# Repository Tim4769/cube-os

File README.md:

# Cube OS

## Members

- Tim
- Pat
- Taiyo

## Description

Cube OS is a desktop robot of 80 x 80 x 80 mm controlled by two legs. It can walk and communicate with other Cube OS robots through online servers using a custom PCB with an ESP32 microcontroller. It supports voice messages, text messages, and remote control features, helping friends stay connected even when they are far apart.

## Features

- Wi-Fi communication between robots via an online server.
- Two 9 g servos power a four-bar walking linkage for bipedal locomotion.
- IMU-assisted stepping, turning, fall detection, and recovery for inertial gait control.
- Ambient Rest Mode with light-aware quiet, privacy, and do-not-disturb behavior.
- Desk climate sensing for local humidity and temperature data.
- Voice Mailbox using the integrated microphone and speaker to record and replay voice notes from friends.
- USB-C power workflow for battery-powered operation, serial debugging, charging, and flashing.
- Camera sharing with OV2640 pictures or brief videos sent to friends or the dashboard.
- Four-face display OS with widgets, expressions, friend feeds, time, status, and air data.
- Remote control so friends can control another Cube OS and interact from far away.

## Justification

Some of our team members are graduating from high school and heading to college after 7 years together at the same school, and we thought, why do not we build something to keep our connection more real and maintain our friend group? Social media and group chats alone make it hard to keep the connection physical, and we will not always have time to fly to each other's cities to meet.

With Cube OS, we aim to keep annoying each other like we used to, in a friendly manner, by controlling each other's robots and sending random noises and messages at 2 am, like crashing into each other's dorm rooms as we used to. With its extra features, it can also serve as a handy desktop companion for productivity or just an accessory for your desk.

## BOM Breakdown

| Item | Qty | Estimate |
| --- | ---: | ---: |
| PCB, minimum production amount | 2 | 144 USD |
| 9 g micro servo motors | 2 | 8 USD |
| OV2640 camera | 1 | 5 USD |
| AS02504AR speaker | 1 | 5 USD |
| 1S 3.7 V LiPo battery | 1 | 6 USD |
| ER-TFT1.54-2 display panels | 4 | 24 USD |
| **Total** |  | **192 USD** |

## Current Status Photos

Current mechanical linkage prototype.

Current PCB layout and component placement.

Current assembled Rev A PCB during USB, firmware, and Wi-Fi power bring-up.

## Project Files

Short index of the main current files. Directory paths, placeholder files, metadata files, scaffold code, TODO files, and planning notes are intentionally excluded.

- PCB source: `PCB/Rev A/source/Cube OS/Cube OS.kicad_pro`, `PCB/Rev A/source/Cube OS/Cube OS.kicad_sch`, `PCB/Rev A/source/Cube OS/Cube OS.kicad_pcb`
- PCB fabrication package: `PCB/Rev A/gerbers/Gerber.zip`, `PCB/Rev A/production/BOM.csv`, `PCB/Rev A/production/CPL.csv`, `PCB/Rev A/production/fabrication_notes.md`
- PCB order package: `PCB/Rev A/order/BOM_manufacture.xls`, `PCB/Rev A/order/ordering contract.pdf`
- PCB 3D export and linked models: `PCB/Rev A/3d_models/PCB 3d model.step`, `PCB/Rev A/source/Cube OS/3D models/`
- Firmware bring-up: `Firmware/platformio.ini`, `Firmware/src/main.cpp`, `Firmware/src/config.h`, `Firmware/src/`
- Sourcing and budget: `BOM/bom.csv`, `BOM/sourcing_notes.md`
- Mechanical assembly: `CAD/Legs/Linkage V2/Assembly/Stepping foot linkage prototype v2.step`
- Current status photos: `Media/Mechanical status 20260511222505_905_44.jpg`, `Media/PCB status 2026-05-28 at 6.02.45 PM.png`, `Media/PCB status 2026-07-15 at 9.23.13 PM.jpg`

## Git LFS

Large binary project assets are tracked with Git LFS through `.gitattributes`, including status photos, CAD/STEP exports, Gerber/drill manufacturing files, archives, PDFs, and spreadsheet order records.

## Placeholder, Scaffold, And Planning Content

These paths are not listed as active project files because they currently contain placeholder files, metadata files, TODO-only files, scaffold code, or planning notes. There is no final project content inside them yet.

- `Software/`
- `Software/src/`
- `Software/screenshots/`

Also excluded from the active project list: `CAD/Legs/Linkage V2/Components/Placeholder Bar.step`.

## License

MIT. See `LICENSE`.

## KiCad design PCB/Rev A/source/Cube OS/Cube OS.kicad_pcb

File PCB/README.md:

# PCB

Cube OS Rev A electrical design, KiCad source, Gerbers, PCBA files, footprints, and linked STEP models.

## Rev A

- Project: `Cube OS`
- KiCad: 9.0
- Board: 60.05 mm x 60.05 mm, 4-layer FR4, 1.599 mm
- Finish: HAL lead-free
- Assembly: top-side SMT and connectors
- Fabrication archive: `Rev A/gerbers/Gerber.zip`
- Order package: `Rev A/order/`

## Active Files

- Source: `Rev A/source/Cube OS/`
- BOM: `Rev A/production/BOM.csv`
- CPL: `Rev A/production/CPL.csv`
- Notes: `Rev A/production/fabrication_notes.md`
- Gerbers: `Rev A/gerbers/Gerber/`
- 3D board export: `Rev A/3d_models/PCB 3d model.step`
- Order records: `Rev A/order/`
- Template/reference data: `Template/`

## Electronics

| Area | Parts |
| --- | --- |
| MCU | ESP32-S3-WROOM-1-N8R8 |
| Displays | Four display FPCs |
| Camera | OV2640 via Amphenol F32R connector |
| Sensors | SHT45, VEML7700, ISM330DHCX, ICS-43434, 10 kOhm NTC |
| Audio | MAX98357A I2S amplifier, JST speaker connector |
| Motion | Two 3-pin servo headers |
| Power | USB-C, 1S LiPo, BQ24074, TPS63802, LDLN025M25R, TPS7A0212 |
| Controls | JS202011JAQN, SPPJ320600 |

## Production Snapshot

- BOM line items: 38
- CPL top-side placements: 45, excluding H1-H4 mounting holes
- Local footprints: `Rev A/source/Cube OS/Cube_OS_Footprint.pretty/`
- Local STEP models: `Rev A/source/Cube OS/3D models/`

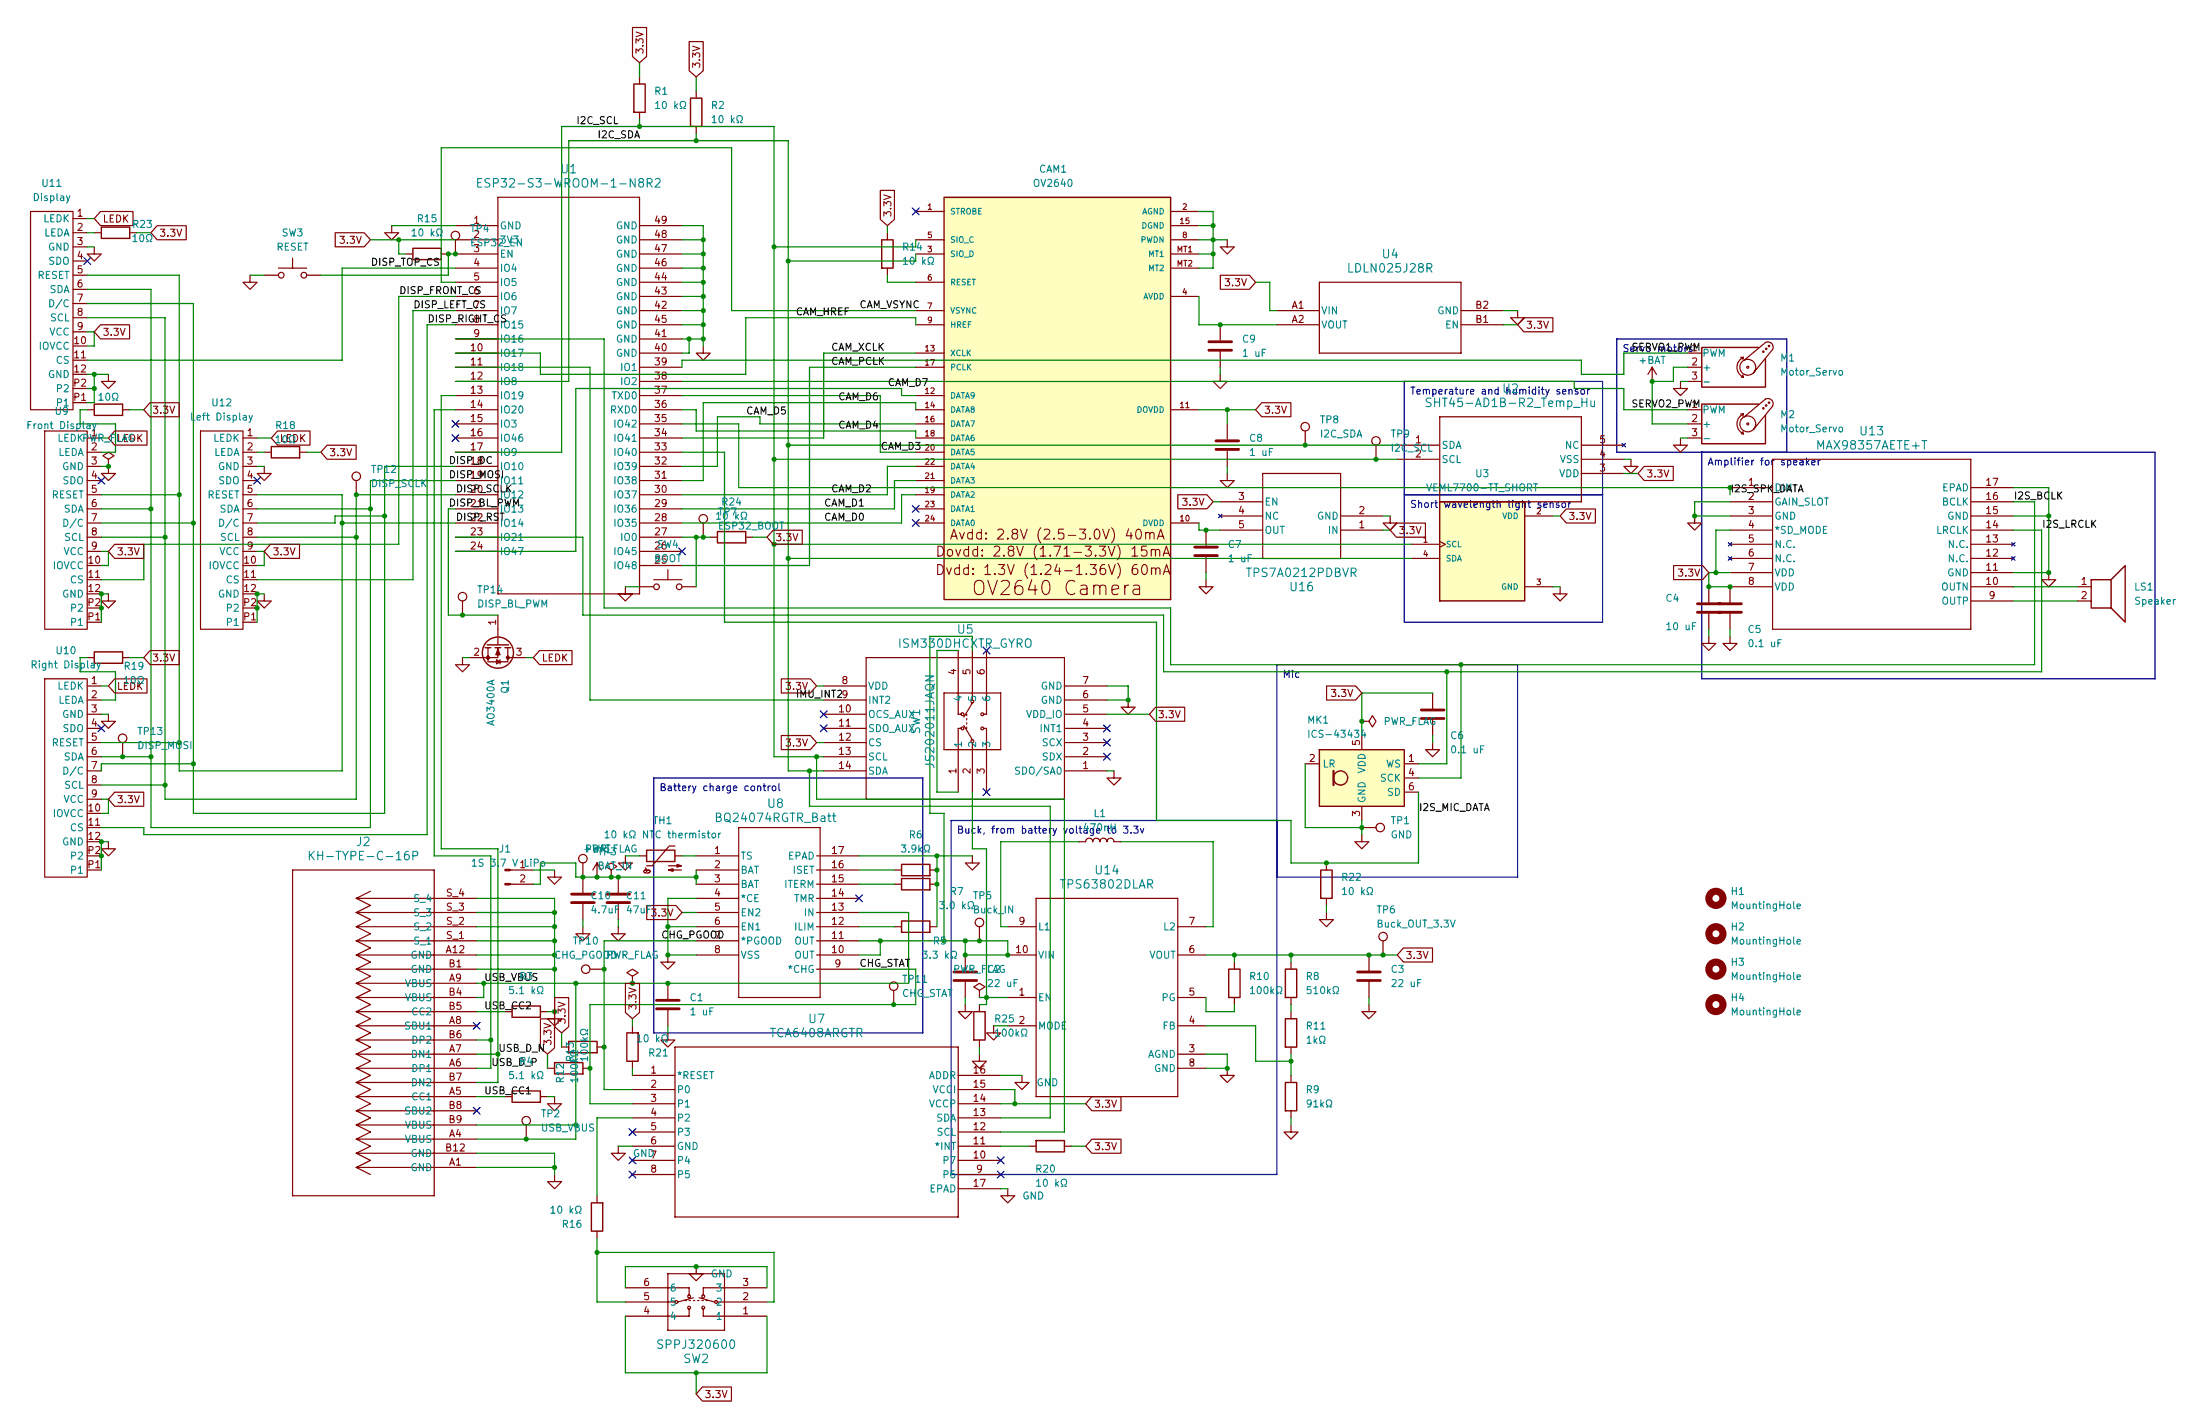
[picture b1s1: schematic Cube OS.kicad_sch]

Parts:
C1, C7, C8, C9: 1 uF; C_0402_1005Metric; JLCPCB C52923
C2, C3: 22 uF; C_0603_1608Metric; JLCPCB C59461
C4: 10 uF; C_0402_1005Metric; JLCPCB C15525
C5, C6: 0.1 uF; C_0402_1005Metric; JLCPCB C1525
C10: 4.7uF; C_0402_1005Metric; JLCPCB C23733
C11: 47uF; C_0805_2012Metric; JLCPCB C16780
CAM1: OV2640; AMPHENOL_F32R-1A7H1-11024; JLCPCB C3167938
H1, H2, H3, H4: MountingHole; MountingHole_2.2mm_M2
J1: 1S 3.7 V LiPo; JST_PH_B2B-PH-K_1x02_P2.00mm_Vertical; JLCPCB C131337
J2: KH-TYPE-C-16P; CONN_KH-TYPE-C_SKE; JLCPCB C709357
L1: 470nH; IND_MWSA0603S_SNL; JLCPCB C408439
LS1: Speaker; JST_PH_B2B-PH-K_1x02_P2.00mm_Vertical; JLCPCB C131337
M1, M2: Motor_Servo; PinHeader_1x03_P2.54mm_Vertical; JLCPCB C49257
MK1: ICS-43434; InvenSense_ICS-43434-6_3.5x2.65mm; JLCPCB C5656610
Q1: AO3400A; SOT-23; JLCPCB C20917
R1, R2, R14, R15, R16, R20, R21, R22, R24: 10 kΩ; R_0402_1005Metric; JLCPCB C25744
R3, R4: 5.1 kΩ; R_0402_1005Metric; JLCPCB C25905
R5: 3.3 kΩ; R_0402_1005Metric; JLCPCB C25890
R6: 3.9kΩ; R_0603_1608Metric; JLCPCB C23018
R7: 3.0 kΩ; R_0603_1608Metric; JLCPCB C4211
R8: 510kΩ; R_0603_1608Metric; JLCPCB C23192
R9: 91kΩ; R_0603_1608Metric; JLCPCB C23265
R10, R12, R13, R25: 100kΩ; R_0402_1005Metric; JLCPCB C25741
R11: 1kΩ; R_0402_1005Metric; JLCPCB C11702
R17, R18, R19, R23: 10Ω; R_0603_1608Metric; JLCPCB C22859
SW1: JS202011JAQN; SWITCH_011CQN; JLCPCB C221662
SW2: SPPJ320600; SPPJ320600_AAL; JLCPCB C470431
SW3: RESET; SW_TS-1088_XNP; JLCPCB C720477
SW4: BOOT; SW_TS-1088_XNP; JLCPCB C720477
TH1: 10 kΩ NTC thermistor; R_0402_1005Metric; JLCPCB C77131
TP1: GND; TestPoint_Pad_1.0x1.0mm
TP2: USB_VBUS; TestPoint_Pad_1.0x1.0mm
TP3: BAT_IN; TestPoint_Pad_1.0x1.0mm
TP4: ESP32_EN; TestPoint_Pad_1.0x1.0mm
TP5: Buck_IN; TestPoint_Pad_1.0x1.0mm
TP6: Buck_OUT_3.3V; TestPoint_Pad_1.0x1.0mm
TP7: ESP32_BOOT; TestPoint_Pad_1.0x1.0mm
TP8: I2C_SDA; TestPoint_Pad_1.0x1.0mm
TP9: I2C_SCL; TestPoint_Pad_1.0x1.0mm
TP10: CHG_PGOOD; TestPoint_Pad_1.0x1.0mm
TP11: CHG_STAT; TestPoint_Pad_1.0x1.0mm
TP12: DISP_SCLK; TestPoint_Pad_1.0x1.0mm
TP13: DISP_MOSI; TestPoint_Pad_1.0x1.0mm
TP14: DISP_BL_PWM; TestPoint_Pad_1.0x1.0mm
U1: ESP32-S3-WROOM-1-N8R2; ESP32-S3-WROOM-1_EXP; JLCPCB C2913204
U2: SHT45-AD1B-R2_Temp_Hu; SHT4x_SEN; JLCPCB C5221601
U3: VEML7700-TT_SHORT; XDCR_VEML7700-TT; PARTREV 1.6; DigiKey_Part_Number 751-VEML7700-TTCT-ND
U4: LDLN025J28R; FLIPCHIP4_0P658X0P658_STM; JLCPCB C2971613
U5: ISM330DHCXTR_GYRO; LGA-14L_STM; JLCPCB C2655101
U7: TCA6408ARGTR; RGT16_1P45X1P45; JLCPCB C181499
U8: BQ24074RGTR_Batt; RGT16_1P7X1P7; JLCPCB C54313
U9: Front Display; CON_5034801200_MOL; JLCPCB C587969
U10: Right Display; CON_5034801200_MOL; JLCPCB C587969
U11: Display; CON_5034801200_MOL; JLCPCB C587969
U12: Left Display; CON_5034801200_MOL; JLCPCB C587969
U13: MAX98357AETE+T; 21-0136I_T1633-4_MXM; JLCPCB C910544
U14: TPS63802DLAR; DLA0010A; JLCPCB C2845237
U16: TPS7A0212PDBVR; SOT23_DBV_TEX; JLCPCB C5220172

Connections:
3.3V: C3.1, C4.1, C5.1, C6.1, C8.1, CAM1.11 (DOVDD), MK1.5 (VDD), R1.1, R2.1, R8.1, R10.1, R12.1, R13.1, R14.1, R15.1, R17.2, R18.2, R19.2, R20.1, R21.2, R23.2, R24.2, SW2.1, SW2.4, TP6.1, U1.2 (3V3), U2.3 (VDD), U3.2 (VDD), U4.A1 (VIN), U4.B1 (EN), U5.5 (VDD_IO), U5.8 (VDD), U5.12 (CS), U7.14 (VCCP), U7.15 (VCCI), U8.5 (EN2), U9.9 (VCC), U9.10 (IOVCC), U10.9 (VCC), U10.10 (IOVCC), U11.9 (VCC), U11.10 (IOVCC), U12.9 (VCC), U12.10 (IOVCC), U13.4 (*SD_MODE), U13.7 (VDD), U13.8 (VDD), U14.6 (VOUT), U16.1 (IN), U16.3 (EN)
+BAT: C10.1, C11.1, J1.2, M1.2 (+), M2.2 (+), TP3.1, U8.2 (BAT), U8.3 (BAT)
/CAM_D0: CAM1.19 (DATA2), U1.28 (IO35)
/CAM_D1: CAM1.21 (DATA3), U1.29 (IO36)
/CAM_D2: CAM1.22 (DATA4), U1.30 (IO37)
/CAM_D3: CAM1.20 (DATA5), U1.37 (TXD0)
/CAM_D4: CAM1.18 (DATA6), U1.36 (RXD0)
/CAM_D5: CAM1.16 (DATA7), U1.32 (IO39)
/CAM_D6: CAM1.14 (DATA8), U1.31 (IO38)
/CAM_D7: CAM1.12 (DATA9), U1.24 (IO47)
/CAM_HREF: CAM1.9 (HREF), U1.10 (IO17)
/CAM_PCLK: CAM1.17 (PCLK), U1.25 (IO48)
/CAM_VSYNC: CAM1.7 (VSYNC), U1.5 (IO5)
/CAM_XCLK: CAM1.13 (XCLK), U1.34 (IO41)
/CHG_PGOOD: R13.2, TP10.1, U7.2 (P0), U8.7 (*PGOOD)
/CHG_STAT: R12.2, TP11.1, U7.3 (P1), U8.9 (*CHG)
/DISP_BL_PWM: Q1.1 (G), TP14.1, U1.21 (IO13)
/DISP_DC: U1.18 (IO10), U9.7 (D/C), U10.7 (D/C), U11.7 (D/C), U12.7 (D/C)
/DISP_FRONT_CS: U1.6 (IO6), U9.11 (CS)
/DISP_LEFT_CS: U1.7 (IO7), U12.11 (CS)
/DISP_MOSI: TP13.1, U1.19 (IO11), U9.6 (SDA), U10.6 (SDA), U11.6 (SDA), U12.6 (SDA)
/DISP_RIGHT_CS: U1.8 (IO15), U10.11 (CS)
/DISP_RST: U1.22 (IO14), U9.5 (RESET), U10.5 (RESET), U11.5 (RESET), U12.5 (RESET)
/DISP_SCLK: TP12.1, U1.20 (IO12), U9.8 (SCL), U10.8 (SCL), U11.8 (SCL), U12.8 (SCL)
/DISP_TOP_CS: U1.4 (IO4), U11.11 (CS)
/I2C_SCL: CAM1.5 (SIO_C), R1.2, TP9.1, U1.17 (IO9), U2.2 (SCL), U3.1 (SCL), U5.13 (SCL), U7.12 (SCL)
/I2C_SDA: CAM1.3 (SIO_D), R2.2, TP8.1, U1.12 (IO8), U2.1 (SDA), U3.4 (SDA), U5.14 (SDA), U7.13 (SDA)
/I2S_BCLK: MK1.4 (SCK), U1.9 (IO16), U13.16 (BCLK)
/I2S_LRCLK: MK1.1 (WS), U1.23 (IO21), U13.14 (LRCLK)
/I2S_MIC_DATA: MK1.6 (SD), R22.1, U1.33 (IO40)
/I2S_SPK_DATA: U1.35 (IO42), U13.1 (DIN)
/IMU_INT2: U1.11 (IO18), U5.9 (INT2)
/SERVO1_PWM: M1.1 (PWM), U1.39 (IO1)
/SERVO2_PWM: M2.1 (PWM), U1.38 (IO2)
/USB_CC1: J2.A5 (CC1), R4.1
/USB_CC2: J2.B5 (CC2), R3.1
/USB_D_N: J2.A7 (DN1), J2.B7 (DN2), U1.13 (IO19)
/USB_D_P: J2.A6 (DP1), J2.B6 (DP2), U1.14 (IO20)
/USB_VBUS: C1.1, J2.A4 (VBUS), J2.A9 (VBUS), J2.B4 (VBUS), J2.B9 (VBUS), TP2.1, U8.13 (IN)
GND: C1.2, C2.2, C3.2, C4.2, C5.2, C6.2, C7.2, C8.2, C9.2, C10.2, C11.2, CAM1.2 (AGND), CAM1.8 (PWDN), CAM1.15 (DGND), CAM1.MT1, CAM1.MT2, J1.1, J2.A1 (GND), J2.A12 (GND), J2.B1 (GND), J2.B12 (GND), J2.S_1, J2.S_2, J2.S_3, J2.S_4, M1.3 (-), M2.3 (-), MK1.2 (LR), MK1.3 (GND), Q1.2 (S), R3.2, R4.2, R5.2, R6.2, R7.2, R9.2, R22.2, R25.2, SW2.3, SW2.6, SW3.1, SW4.1, TH1.1, TP1.1, U1.1 (GND), U1.40 (GND), U1.41 (GND), U1.42 (GND), U1.43 (GND), U1.44 (GND), U1.45 (GND), U1.46 (GND), U1.47 (GND), U1.48 (GND), U1.49 (GND), U2.4 (VSS), U3.3 (GND), U4.B2 (GND), U5.1 (SDO/SA0), U5.6 (GND), U5.7 (GND), U7.6 (GND), U7.16 (ADDR), U7.17 (EPAD), U8.4 (*CE), U8.6 (EN1), U8.8 (VSS), U8.17 (EPAD), U9.3 (GND), U9.12 (GND), U9.P1, U9.P2, U10.3 (GND), U10.12 (GND), U10.P1, U10.P2, U11.3 (GND), U11.12 (GND), U11.P1, U11.P2, U12.3 (GND), U12.12 (GND), U12.P1, U12.P2, U13.2 (GAIN_SLOT), U13.3 (GND), U13.11 (GND), U13.15 (GND), U13.17 (EPAD), U14.2 (MODE), U14.3 (AGND), U14.8 (GND), U16.2 (GND)
LEDK: Q1.3 (D), U9.1 (LEDK), U10.1 (LEDK), U11.1 (LEDK), U12.1 (LEDK)
unnamed: C9.1, CAM1.4 (AVDD), U4.A2 (VOUT)
unnamed: C7.1, CAM1.10 (DVDD), U16.5 (OUT)
unnamed: CAM1.6 (RESET), R14.2
unnamed: R8.2, R11.1
unnamed: R16.1, SW2.2, SW2.5
unnamed: SW1.1, SW1.4
unnamed: R15.2, SW3.2, TP4.1, U1.3 (EN)
unnamed: R24.1, SW4.2, TP7.1, U1.27 (IO0)
unnamed: R20.2, U7.11 (*INT)
unnamed: R21.1, U7.1 (*RESET)
unnamed: R16.2, U7.4 (P2)
unnamed: R5.1, U8.12 (ILIM)
unnamed: R6.1, U8.16 (ISET)
unnamed: R7.1, U8.15 (ITERM)
unnamed: TH1.2, U8.1 (TS)
unnamed: R17.1, U9.2 (LEDA)
unnamed: R19.1, U10.2 (LEDA)
unnamed: R23.1, U11.2 (LEDA)
unnamed: R18.1, U12.2 (LEDA)
unnamed: LS1.1, U13.10 (OUTN)
unnamed: LS1.2, U13.9 (OUTP)
unnamed: R25.1, SW1.2, U14.1 (EN)
unnamed: R9.1, R11.2, U14.4 (FB)
unnamed: L1.1, U14.9 (L1)
unnamed: L1.2, U14.7 (L2)
unnamed: R10.2, U14.5 (PG)
unnamed: C2.1, SW1.5, TP5.1, U8.10 (OUT), U8.11 (OUT), U14.10 (VIN)

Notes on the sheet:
Buck, from battery voltage to 3.3v
Battery charge control
Amplifier for speaker
Temperature and humidity sensor
Mic
Servo motors
Short wavelength light sensor

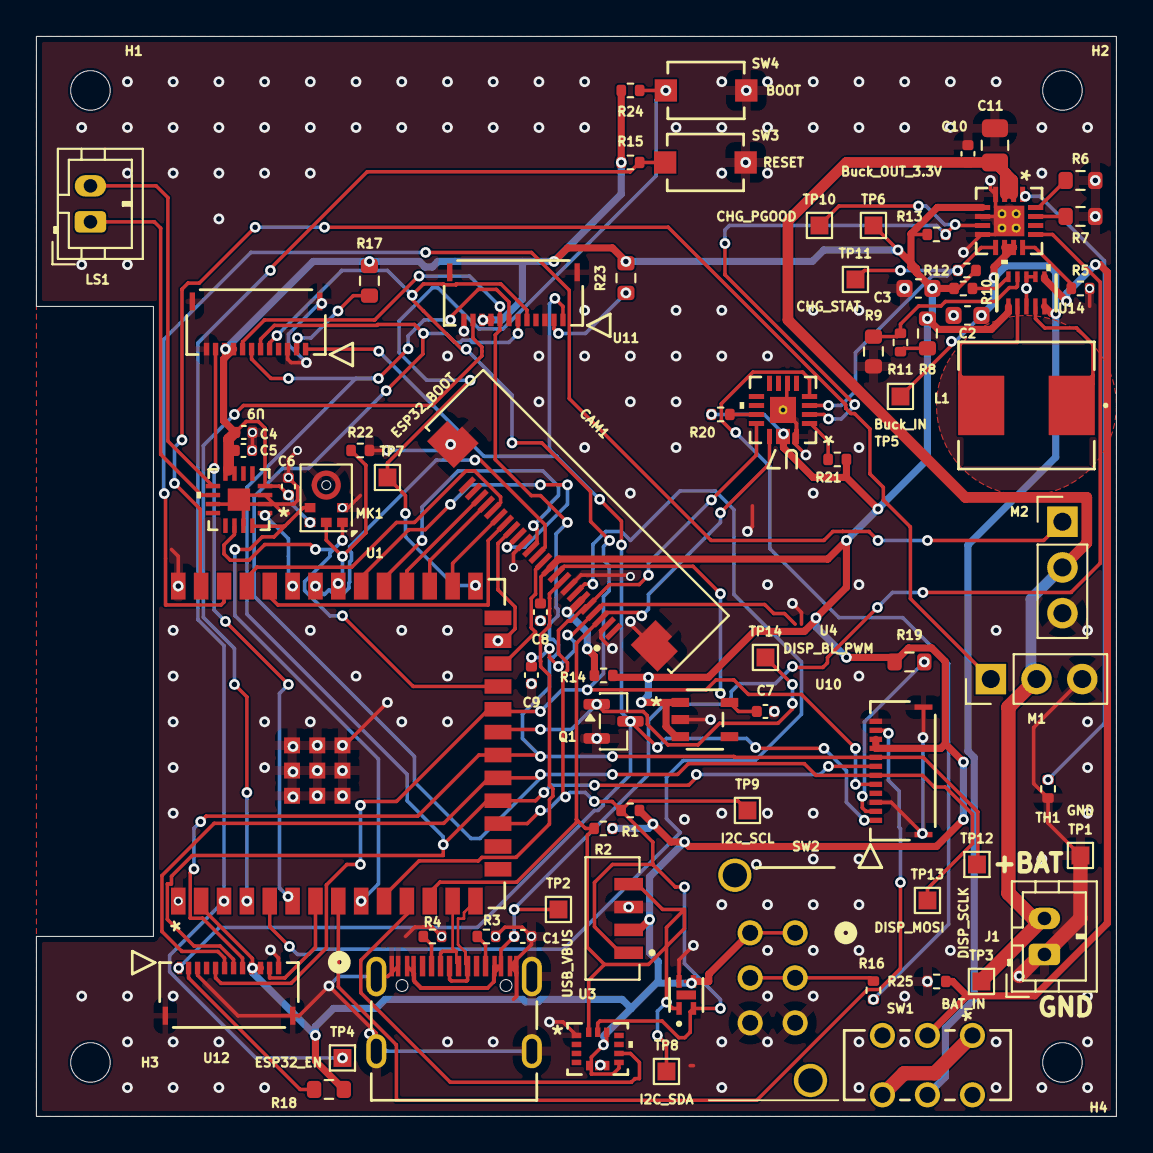
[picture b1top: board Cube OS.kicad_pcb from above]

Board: 4 copper layers, 60.0 x 60.0 mm, 82 parts (0 on the bottom side), 68 nets.

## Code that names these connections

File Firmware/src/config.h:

#pragma once

#define SERIAL_BAUD_RATE 115200

// Setup access point details. These are only used when the ESP32 needs Wi-Fi setup.
constexpr const char* AP_NAME = "CubeOS-Setup";
constexpr const char* AP_PASSWORD = "12345678";

// mDNS lets a browser open http://cubeos.local instead of typing the numeric IP address.
constexpr const char* MDNS_NAME = "cubeos";

// Names used inside ESP32 NVS flash storage for the saved Wi-Fi credentials.
constexpr const char* WIFI_NAMESPACE = "wifi";
constexpr const char* WIFI_SSID_KEY = "ssid";
constexpr const char* WIFI_PASSWORD_KEY = "password";
constexpr const char* WIFI_CONFIGURED_KEY = "configured";

// Timing values are in milliseconds.
constexpr unsigned long BOOT_STABILIZE_DELAY_MS = 3000;
constexpr unsigned long WIFI_CONNECT_TIMEOUT_MS = 15000;
constexpr unsigned long WIFI_CONNECT_CHECK_INTERVAL_MS = 500;
constexpr unsigned long MDNS_RETRY_INTERVAL_MS = 5000;

// The web server listens on port 80, the normal HTTP port.
constexpr int WEB_SERVER_PORT = 80;

constexpr int PIN_UNASSIGNED = -1;

// Rev A has no separate status LED GPIO in the schematic.
// Do not use GPIO48 for status LED: GPIO48 is CAM_PCLK.
constexpr int STATUS_LED_PIN = PIN_UNASSIGNED;

// Shared I2C/SCCB bus.
constexpr int I2C_SDA_PIN = 8;
constexpr int I2C_SCL_PIN = 9;

// Four display connectors share MOSI/SCLK/DC/reset/backlight and use separate CS pins.
constexpr int DISPLAY_TOP_CS_PIN = 4;
constexpr int DISPLAY_FRONT_CS_PIN = 6;
constexpr int DISPLAY_LEFT_CS_PIN = 7;
constexpr int DISPLAY_RIGHT_CS_PIN = 15;
constexpr int DISPLAY_DC_PIN = 10;
constexpr int DISPLAY_MOSI_PIN = 11;
constexpr int DISPLAY_SCLK_PIN = 12;
constexpr int DISPLAY_BACKLIGHT_PWM_PIN = 13;
constexpr int DISPLAY_RESET_PIN = 14;

// I2S audio: ICS-43434 microphone and MAX98357A speaker amplifier.
constexpr int I2S_BCLK_PIN = 16;
constexpr int I2S_LRCLK_PIN = 21;
constexpr int I2S_MIC_DATA_PIN = 40;
constexpr int I2S_SPK_DATA_PIN = 42;

// ISM330DHCX interrupt lines.
// INT1 is not connected in the latest Rev A schematic.
constexpr int IMU_INT1_PIN = PIN_UNASSIGNED;
constexpr int IMU_INT2_PIN = 18;

// Servo connector PWM pins.
constexpr int MOVEMENT_SERVO1_PWM_PIN = 1; // M1
constexpr int MOVEMENT_SERVO2_PWM_PIN = 2; // M2

// Only assign these after confirming which physical servo is left/right.
constexpr int MOVEMENT_LEFT_SERVO_PIN = PIN_UNASSIGNED;
constexpr int MOVEMENT_RIGHT_SERVO_PIN = PIN_UNASSIGNED;

// User/control and charger status lines are on the TCA6408 I2C GPIO expander,
// not direct ESP32 GPIOs.
constexpr int USER_SWITCH_PIN = PIN_UNASSIGNED;
constexpr int CHARGER_PGOOD_PIN = PIN_UNASSIGNED;
constexpr int CHARGER_STAT_PIN = PIN_UNASSIGNED;

constexpr int IO_EXPANDER_CHARGER_PGOOD_PIN = 0;
constexpr int IO_EXPANDER_CHARGER_STAT_PIN = 1;
constexpr int IO_EXPANDER_USER_SWITCH_PIN = 2;

// OV2640 camera parallel bus and clock/sync pins.
constexpr int CAMERA_D0_PIN = 35;
constexpr int CAMERA_D1_PIN = 36;
constexpr int CAMERA_D2_PIN = 37;
constexpr int CAMERA_D3_PIN = 43; // schematic pin function TXD0
constexpr int CAMERA_D4_PIN = 44; // schematic pin function RXD0
constexpr int CAMERA_D5_PIN = 39;
constexpr int CAMERA_D6_PIN = 38;
constexpr int CAMERA_D7_PIN = 47;
constexpr int CAMERA_HREF_PIN = 17;
constexpr int CAMERA_PCLK_PIN = 48;
constexpr int CAMERA_VSYNC_PIN = 5;
constexpr int CAMERA_XCLK_PIN = 41;
constexpr int CAMERA_RESET_PIN = PIN_UNASSIGNED; // pulled up by R14
constexpr int CAMERA_PWDN_PIN = PIN_UNASSIGNED;  // tied to GND

// Native USB pins. Keep these reserved for USB.
constexpr int USB_D_N_PIN = 19;
constexpr int USB_D_P_PIN = 20;

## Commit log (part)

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2026-05-08 Scaffold hardware project repo
2026-05-10 reorganised V2 linkage and uploaded V1 linkage for version iterations
2026-05-11 Add Rev A hardware files and concise docs
2026-05-11 Update README with current status photos
2026-05-18 Update Rev A hardware files
2026-05-18 Add Wi-Fi setup access point
2026-05-18 Add ESP32 Wi-Fi dashboard setup flow
2026-05-19 Add Rev A pin map guide
2026-05-19 Modularize firmware runtime
    Split dashboard, network, movement, and boot orchestration into separate modules.
    Add Rev A pin constants, IMU library dependencies, and initial servo movement test hooks.
2026-05-19 Remove placeholder journal entries
2026-05-19 Remove Journal directory placeholder
2026-05-23 Update firmware pin map for Rev A
2026-05-23 Update Rev A PCB production package
2026-05-23 Revert "Update Rev A PCB production package"
    This reverts commit 683648053a19518fab4d864910172dd1a356c20e.
2026-05-28 Add Rev A order package docs
2026-05-28 Update project assets and LFS tracking
2026-05-28 added linkage v3 and body files
